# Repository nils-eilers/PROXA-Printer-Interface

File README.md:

PROXA Printer Interface
=======================

This project contains all required files for a modern version of a
vintage printer interface originally made by Helmut Proxa's ULTRA
ELECTRONIC. In the early 80's, it was *the* preferred printer
interface to connect a Centronics compatible printer to a Commodore CBM/PET
to the IEEE-488 bus.

Back then, it was cloned by many other firms several times without permission.
This time, Helmut Proxa kindly allowed me to rebuild his interface and
explained me his very clever circuit in great detail. Though the [original
schematics] (http://www.forum64.de/wbb4/index.php?thread/57196-drucken-mit-cbm-rechnern/&postID=844718#post844718)
were available, I had no access to a dump of the original EPROM contents,
so this part had to been developed again. What's more, I also developed
a command line program for Linux / OS X / Windows which generates the
EPROM contents driven by a configuration file. This enables the user
to re-map the character conversion to suit his personal needs.

Nils Eilers, February 2016

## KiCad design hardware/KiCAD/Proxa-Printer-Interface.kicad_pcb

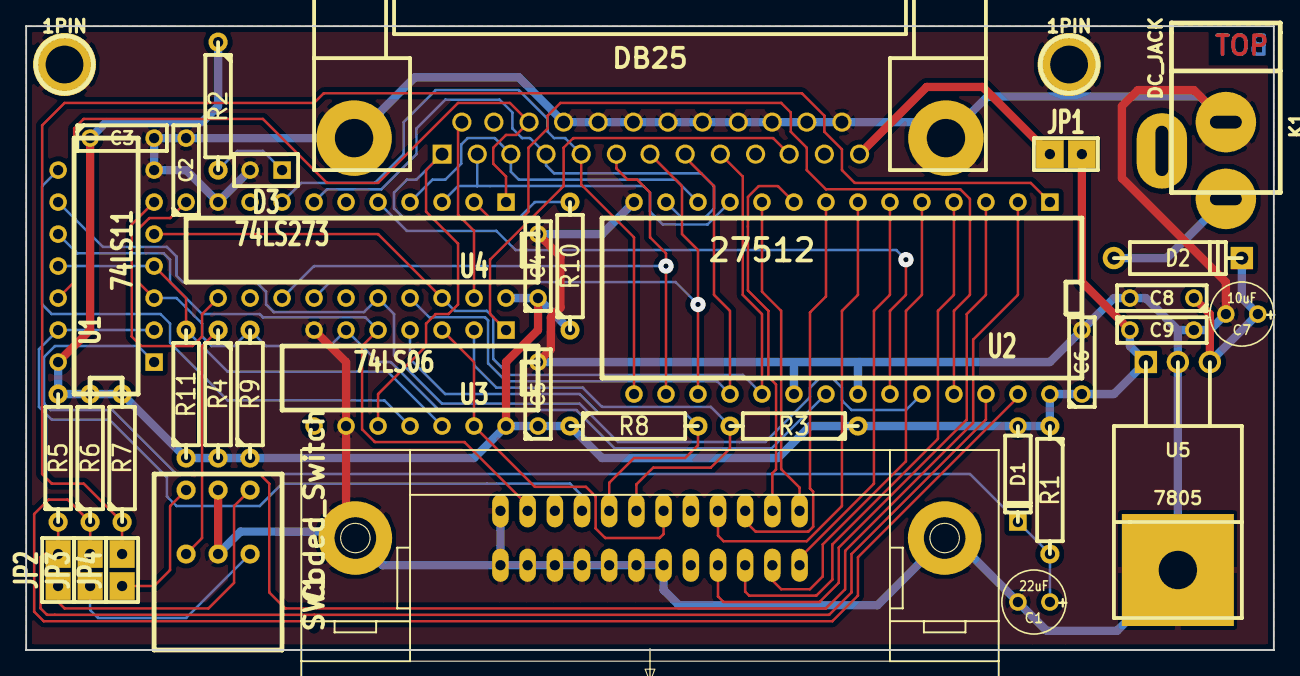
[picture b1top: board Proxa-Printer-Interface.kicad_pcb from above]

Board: 2 copper layers, 99.1 x 49.5 mm, 38 parts (0 on the bottom side), 46 nets.

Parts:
1PIN, 1PIN#2: P***; 1pin
C1: 22uF; C1V5
C2, C3, C4, C5, C6, C8, C9: 100nF; C2
C7: 10uF; C1V5
D1: 1N4148; D3
D2: 1N4001; D4
D3: LED; SIL-2
J1: DB25; DB25FC
J2: C24H; con-amp-champ-24HP
JP1, JP2, JP3, JP4: BREAKER; SIL-2
K1: DC_JACK; JACK_ALIM
R1, R3, R4, R5, R6, R7, R8, R9, R10, R11: 10k; R4
R2: 560R; R4
SW1: Coded_Switch; ENCSW
U1: 74LS11; DIP-14__300
U2: 27512; DIP-28__600
U3: 74LS06; DIP-14__300
U4: 74LS273; DIP-20__300
U5: 7805; TO220

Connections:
/A12: R4.1, SW1.2, U2.2
/A13: JP2.2, R5.1, U2.26
/A14: JP3.2, R6.1, U2.27
/A15: JP4.2, R7.1, U2.1
/ATN: J2.11, U1.10, U3.5
/BUSY: J1.11, U3.1
/D0: J1.2, U2.11, U4.3
/D1: J1.3, U2.12, U4.4
/D2: J1.4, U2.13, U4.7
/D3: J1.5, U2.15, U4.8
/D4: J1.6, U2.16, U4.13
/D5: J1.7, U2.17, U4.14
/D6: J1.8, U2.18, U4.17
/D7: J1.9, U1.5, U2.19, U4.18
/DAV: J2.6, U3.3, U3.13
/I0: J2.1, U2.10
/I1: J2.2, U2.9
/I2: J2.3, U2.8
/I3: J2.4, U2.7
/I4: J2.13, U2.6
/I5: J2.14, U2.5
/I6: J2.15, U2.4
/I7: J2.16, U2.3
/IFC: J2.9, U1.2, U1.13
/NDAC: J2.8, R8.2, U3.4
/NRFD: J2.7, R3.2, U3.2
/Q0: U2.25, U4.2
/Q1: U2.23, U4.5
/Q6: U1.9, U2.24, U4.16
/~AUTOFD: J1.14, U4.19
/~RESET: J1.16, U1.12, U4.1
/~STROBE: J1.1, R10.2, U3.10
GND: 1PIN.1, 1PIN#2.1, C1.2, C2.2, C3.2, C4.2, C5.2, C6.2, C7.2, C8.2, C9.2, D3.2, J1.17, J1.18, J1.19, J1.20, J1.21, J1.22, J1.23, J1.24, J1.25, J2.12, J2.18, J2.19, J2.20, J2.21, J2.22, J2.23, J2.24, K1.2, SW1.1, U1.7, U2.14, U2.20, U2.22, U3.7, U3.9, U4.10, U5.2, U5.4
unnamed: U1.8, U3.11
unnamed: JP4.1, SW1.5
unnamed: J1.13, JP1.1
unnamed: D3.1, R2.2
unnamed: JP2.1, SW1.3
unnamed: JP3.1, SW1.4
unnamed: D2.1, K1.1
unnamed: C7.1, C8.1, D2.2, U5.3
unnamed: C2.1, R9.2, U1.3, U2.21, U3.6
unnamed: R11.2, U1.4, U1.11, U3.12
unnamed: U1.6, U4.11
unnamed: C1.1, D1.2, R1.2, U1.1
VCC: C3.1, C4.1, C5.1, C6.1, C9.1, D1.1, JP1.2, R1.1, R2.1, R3.1, R4.2, R5.2, R6.2, R7.2, R8.1, R9.1, R10.1, R11.1, U1.14, U2.28, U3.14, U4.20, U5.1

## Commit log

2019-11-12 Add EPROM binary and EXE to generate it
